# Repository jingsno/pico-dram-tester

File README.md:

# Pico DRAM Tester

Having trouble with your old-school DIP dynamic RAM chips? Here's a simple
RAM tester that will give you a definitive pass or fail for a variety of
chips.

**New** rev 3 now available! New features include:

* USB-C power connector with PD resistors
* Universal encoder wiring supports Bourns and Panasonic style encoders
* Through-hole footprint for the Pico2 to ease soldering

Benefits

* Tests RAM *at full speed* so you can feel confident about a chip that passes.
* Easy to construct with widely-available parts. No surface mount chips.
* Low cost
* Built-in DC-DC modules generate extra voltages required by 4116-class chips
* Can be operated from a bench supply for voltage margin testing

Supported Devices

* 4027 (4K x 1)
* 4108 (8K x 1 that are 4116s with only half test good: MK4108, TMS4108, etc)
* 4116 (16K x 1)
* 4132 (32K x 1, piggyback)
* 4132 (32K x 1 that are 4164s with only half tested good: TMS4532, M3732)
* 4164 (64K x 1)
* 41128 (128K x 1, piggyback)
* 41256 (256K x 1)
* 4416 (16K x 4)
* 4464 (64K x 4)
* 44256 (256K x 4)

Out of scope

* SRAM, DRAM chips larger than 1MBit
* Logic chips

## Construction

[Fab package](fab/pico-dram-tester-rev3.zip)

[Schematic](pico-dram-tester.pdf)

[Bill of Materials](pico-dram-tester.csv)

The board is a simple 2-layer board, 100mm x 100mm, and 1.6mm thick. Fabricate
at your favorite vendor in any color you wish.

You may populate the board only with the sockets for devices you plan to use,
or you may populate all the sockets. You can try substituting the sockets with
standard IC sockets, but I recommend ZIF sockets which are much easier to use.
Why so many sockets? It saves you from having to install dozens of pin control
transistors required to make a tester work with a single universal socket.

If you want to populate the USB-C connector, do it first before any other
components. It makes it much easier to access the surface-mount pins along
the edge with a soldering iron.

Populate Q1, U7, U8, R2, R3, R4, and R5 if you would like to test 4116 and
4132 devices without requiring an external -5V and +12V power supply.

If you want to provide the -5V, +5V, and +12V power from your bench supply,
then you may leave those components off of the board and connect your power
leads to the -5V, +5V, and +12V test points. If you don't plan to test 4116
or 4132 chips, then you can safely leave out those components.

The LCD display is nominally the [Adafruit 4383](https://www.adafruit.com/product/4383) which is to be installed at location J1 (U9 is not required when using
this display). You can also use cheaper devices available from Aliexpress and
others. They are 8-pin LCD displays sold as 1.14" 135x240 IPS ST7789 modules.
Install this display at position J2. You may also need to add the voltage
monitor at position U9.

For several reasons, this board requires a Pico 2 microcontroller board and
will not work at all with the Pico 1.

If you use a Bourns-style encoder, you will need to solder across the jumper
on the back of the board. **This is the most common type of cheaply-available
encoders, so you probably want to do this.** Otherwise, for Panasonic-style
encoders, leave this open.

After installing all the components and inspecting the board for accidental
short circuits, connect the Pico 2 via the USB connector to a computer. The
device should power up and appear as a USB mass storage device. Copy the
prebuilt firmware file [pmemtest.uf2](firmware/pmemtest.uf2) to this device, and the Pico 2 will
program itself. Reset the power and you should see a menu of chips on the LCD
screen.

## Using the DRAM Tester

Before starting, connect the tester to a power source:

* If you did not install U7 and U8, connect a bench supply to the GND, -5V, +5V, and +12V test points. Connect the Pico 2 USB jack to a power adapter or computer.
* If you installed U7 and U8, connect a 5V bench supply to the 5VIN and GND test points. Instead of a bench supply, you could connect the Pico 2 USB jack to a power adapter, but you won't be able to control the voltage. A computer often has a much lower voltage and you may fail RAM chips that actually function at 5V.

1. Install the chip in the socket designated for that type of memory chip, following the pin 1 orientation (the pin 1 notch faces the ZIF socket lever). Note that some of the sockets are used for several types of memory.
2. Rotate the selection knob until the correct part number is highlighted, and push down on the top of the selection knob (it's also a button!)
3. If you make a mistake, press the button to the left of the selection knob to go back.
4. After selecting a part, you need to pick the correct speed grade to run the
test. Often the speed grade is marked on the chip as a suffix. For example, -15
typically means 150ns. If you're not sure, pick the slowest speed.
5. If you are using an external bench power supply to supply -5V and +12V, turn it on now. If you soldered in the on-board voltage converter modules, you don't need to do anything. Push the top of the selection knob to continue.
6. The test runs. You will see a red "X" if the test fails or a green checkmark if the test passes.
7. You can rerun the test immediately by pushing down on the top of the selection knob. Or go back to the menu by pushing the button to the left.

Note: The visualization pane on the left is just for entertainment and doesn't
really represent bad bits.

## Technical Details

The Pico 2 microcontroller (RP2350) has built-in high-speed PIO processors
which are overclocked to 300MHz. This means that the DRAM timing can be set
to a resolution of 3.3ns. The RAM test runs on the second CPU core, decoupling
it from the GUI, which runs on the first CPU core.

RAM testing can be surprisingly complicated. There are many kinds of failures:

* Stuck-at fault - a cell is stuck at a 1 or a 0
* Stuck-open fault - a cell isn't connected (input or output)
* Transition fault - a cell can't go from one state to another (1 to 0 or 0 to 1)
* Data retention fault - a cell flips after a time delay
* Coupling fault - the state of one cell affects the state of another
* Neighborhood pattern sensitive fault - a specific pattern in nearby cells causes a cell to flip
* Address decoder fault - cells may be isolated, or multiple cells accessed at the same address, or multiple addresses may access a single cell

There are a number of "traditional" RAM tests such as the checkerboard or
walking 1/0, but these tests can be slow and don't have precise coverage over
all failure modes. The Pico DRAM Tester uses more modern testing algorithms:

* March-B. This is a sequence of linear reads and writes designed to catch address faults, stuck-at faults, transition faults, and coupling faults.
* Pseudorandom test. This test loads a pseudorandom number sequence into the memory, reads it back, and checks to make sure it didn't change. The test is repeated with 64 different pseudorandom patterns to enhance coverage. The patterns are identical between runs, making the test repeatable. The test only uses pseudorandom data and does not randomize the address. This test can detect many pattern-sensitive faults.
* Refresh test. This test loads a pattern into the memory, waits for a time delay, and then tries to read it back. The time delay is longer than a typical refresh rate. This test can detect data retention faults.

## Known Issues

* The 41128 test is not yet reliable.

## Troubleshooting

Check your solder connections. Does the Pico 2 board show up in bootloader mode when you plug it into a computer?

The Pico DRAM Tester uses an overclocked Pico 2 configuration.
Some Pico 2 boards may not work well at 300MHz, crashing or not drawing the GUI on the screen correctly.
You may be able to get it working by editing pmemtest.c, find the line `vreg_set_voltage(VREG_VOLTAGE_1_15);` and change the voltage setting to `VREG_VOLTAGE_1_20`.

## License

This work is licensed under a Creative Commons Attribution-ShareAlike 4.0
International License. See [https://creativecommons.org/licenses/by-sa/4.0/](https://creativecommons.org/licenses/by-sa/4.0/).

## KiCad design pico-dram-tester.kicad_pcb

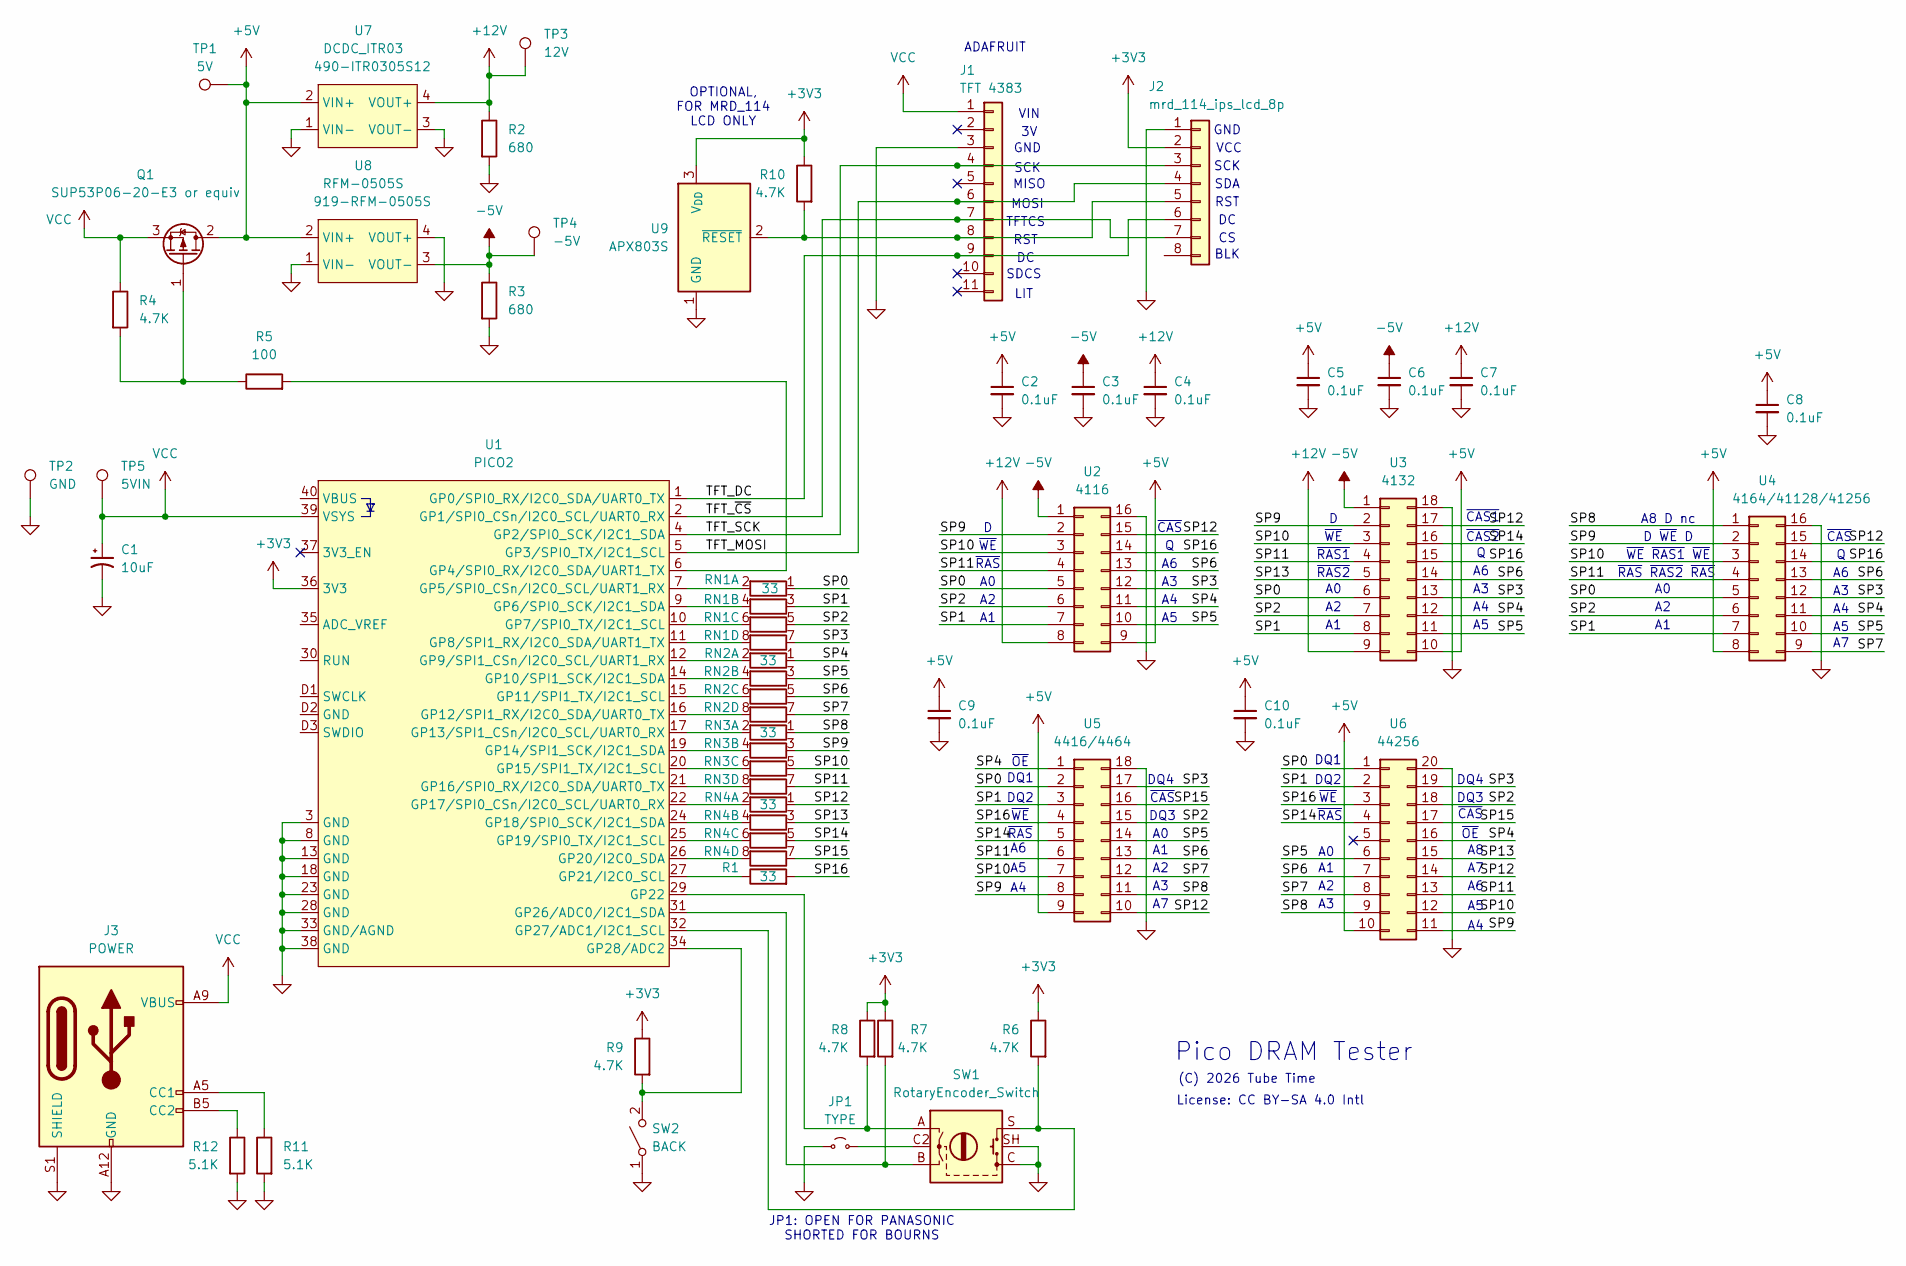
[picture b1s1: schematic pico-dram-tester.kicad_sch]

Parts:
C1: 10uF; CAPAE200P500X1100; Mouser 667-ECA-1VM100
C2, C3, C4, C5, C6, C7, C8, C9, C10: 0.1uF; CAPAC200; Mouser 80-C322C104M5U
J1: TFT 4383; ADAFRUIT_4383
J2: mrd_114_ips_lcd_8p; PinHeader_1x08_P2.54mm_Vertical
J3: POWER; USB_C_Receptacle_GCT_USB4125-xx-x-0190_6P_TopMnt_Horizontal; Mouser 179-UJCHGSMT1P6TR
JP1: TYPE; SolderJumper-2_P1.3mm_Open_Pad1.0x1.5mm
Q1: SUP53P06-20-E3 or equiv; TO-220-3_Vertical; Mouser 781-SUP53P06-20-E3
R1: 33; RESA500; Mouser 594-MBB02070C3309FCT
R2, R3: 680; RESA500; Mouser 594-MBB02070C6800FCT
R4, R6, R7, R8, R9, R10: 4.7K; RESA500; Mouser 594-MBB02070C4701FCT
R5: 100; RESA500; Mouser 594-MBB02070C1000FCT
R11, R12: 5.1K; RESA500; Mouser 594-MBB02070C5101FCT
RN1, RN2, RN3, RN4: 33; R_Array_SIP8; Mouser 652-4608X-2LF-33
SW1: RotaryEncoder_Switch; ENCODER_SW_UNIV
SW2: BACK; SW_SPST_Omron_B3F-50xx; Mouser 653-B3F-4005
TP1: 5V; TestPoint_Keystone_5005-5009_Compact; Mouser 534-5005
TP2: GND; TestPoint_Keystone_5005-5009_Compact; Mouser 534-5006
TP3: 12V; TestPoint_Keystone_5005-5009_Compact; Mouser 534-5009
TP4: -5V; TestPoint_Keystone_5005-5009_Compact; Mouser 534-5007
TP5: 5VIN; TestPoint_Keystone_5005-5009_Compact; Mouser 534-5005
U1: PICO2; Pico2_PTH; Mouser 358-SC1631
U2: 4116; DIP_Socket-16_W4.3_W5.08_W7.62_W10.16_W10.9_3M_216-3340-00-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
U3: 4132; DIP_Socket-18_W4.3_W5.08_W7.62_W10.16_W10.9_3M_218-3341-00-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
U4: 4164/41128/41256; DIP_Socket-16_W4.3_W5.08_W7.62_W10.16_W10.9_3M_216-3340-00-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
U5: 4416/4464; DIP_Socket-18_W4.3_W5.08_W7.62_W10.16_W10.9_3M_218-3341-00-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
U6: 44256; DIP_Socket-20_W4.3_W5.08_W7.62_W10.16_W10.9_3M_220-3342-00-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
U7: DCDC_ITR03; Mouser 490-ITR0305S12
U8: RFM-0505S; DCDC_ITR03; Mouser 919-RFM-0505S
U9: APX803S; SOT-23_Handsoldering; Mouser 621-APX803S-29SA-7

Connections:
+3V3: J2.2, R6.1, R7.1, R8.1, R9.1, R10.1, U1.36 (3V3), U9.3 (V_{DD})
+5V: C2.1, C5.1, C8.1, C9.1, C10.1, Q1.2 (D), TP1.1, U2.9, U3.10, U4.8, U5.9, U6.10, U7.2 (VIN+), U8.2 (VIN+)
+12V: C4.1, C7.1, R2.1, TP3.1, U2.8, U3.9, U7.4 (VOUT+)
-5V: C3.1, C6.1, R3.1, TP4.1, U2.1, U3.1, U8.3 (VOUT-)
/SP0: RN1.1 (R1.1), U2.5, U3.6, U4.5, U5.2, U6.1
/SP1: RN1.3 (R2.1), U2.7, U3.8, U4.7, U5.3, U6.2
/SP2: RN1.5 (R3.1), U2.6, U3.7, U4.6, U5.15, U6.18
/SP3: RN1.7 (R4.1), U2.12, U3.13, U4.12, U5.17, U6.19
/SP4: RN2.1 (R1.1), U2.11, U3.12, U4.11, U5.1, U6.16
/SP5: RN2.3 (R2.1), U2.10, U3.11, U4.10, U5.14, U6.6
/SP6: RN2.5 (R3.1), U2.13, U3.14, U4.13, U5.13, U6.7
/SP7: RN2.7 (R4.1), U4.9, U5.12, U6.8
/SP8: RN3.1 (R1.1), U4.1, U5.11, U6.9
/SP9: RN3.3 (R2.1), U2.2, U3.2, U4.2, U5.8, U6.11
/SP10: RN3.5 (R3.1), U2.3, U3.3, U4.3, U5.7, U6.12
/SP11: RN3.7 (R4.1), U2.4, U3.4, U4.4, U5.6, U6.13
/SP12: RN4.1 (R1.1), U2.15, U3.17, U4.15, U5.10, U6.14
/SP13: RN4.3 (R2.1), U3.5, U6.15
/SP14: RN4.5 (R3.1), U3.16, U5.5, U6.4
/SP15: RN4.7 (R4.1), U5.16, U6.17
/SP16: R1.2, U2.14, U3.15, U4.14, U5.4, U6.3
/TFT_DC: J1.9, J2.6, U1.1 (GP0/SPI0_RX/I2C0_SDA/UART0_TX)
/TFT_MOSI: J1.6, J2.4, U1.5 (GP3/SPI0_TX/I2C1_SCL)
/TFT_SCK: J1.4, J2.3, U1.4 (GP2/SPI0_SCK/I2C1_SDA)
/TFT_~CS: J1.7, J2.7, U1.2 (GP1/SPI0_CSn/I2C0_SCL/UART0_RX)
GND: C1.2, C2.2, C3.2, C4.2, C5.2, C6.2, C7.2, C8.2, C9.2, C10.2, J1.3, J2.1, J3.A12 (GND), J3.B12 (GND), J3.S1 (SHIELD), JP1.1 (A), R2.2, R3.2, R11.2, R12.2, SW1.C, SW1.SH, SW2.1 (A), TP2.1, U1.3 (GND), U1.8 (GND), U1.13 (GND), U1.18 (GND), U1.23 (GND), U1.28 (GND), U1.33 (GND/AGND), U1.38 (GND), U2.16, U3.18, U4.16, U5.18, U6.20, U7.1 (VIN-), U7.3 (VOUT-), U8.1 (VIN-), U8.4 (VOUT+), U9.1 (GND)
unnamed: J1.8, J2.5, R10.2, U9.2 (~RESET)
unnamed: J3.A5 (CC1), R11.1
unnamed: J3.B5 (CC2), R12.1
unnamed: JP1.2 (B), SW1.C2 (C)
unnamed: Q1.1 (G), R4.2, R5.1
unnamed: RN1.2 (R1.2), U1.7 (GP5/SPI0_CSn/I2C0_SCL/UART1_RX)
unnamed: RN1.4 (R2.2), U1.9 (GP6/SPI0_SCK/I2C1_SDA)
unnamed: RN1.6 (R3.2), U1.10 (GP7/SPI0_TX/I2C1_SCL)
unnamed: RN1.8 (R4.2), U1.11 (GP8/SPI1_RX/I2C0_SDA/UART1_TX)
unnamed: RN2.2 (R1.2), U1.12 (GP9/SPI1_CSn/I2C0_SCL/UART1_RX)
unnamed: RN2.4 (R2.2), U1.14 (GP10/SPI1_SCK/I2C1_SDA)
unnamed: RN2.6 (R3.2), U1.15 (GP11/SPI1_TX/I2C1_SCL)
unnamed: RN2.8 (R4.2), U1.16 (GP12/SPI1_RX/I2C0_SDA/UART0_TX)
unnamed: RN3.2 (R1.2), U1.17 (GP13/SPI1_CSn/I2C0_SCL/UART0_RX)
unnamed: RN3.4 (R2.2), U1.19 (GP14/SPI1_SCK/I2C1_SDA)
unnamed: RN3.6 (R3.2), U1.20 (GP15/SPI1_TX/I2C1_SCL)
unnamed: RN3.8 (R4.2), U1.21 (GP16/SPI0_RX/I2C0_SDA/UART0_TX)
unnamed: RN4.2 (R1.2), U1.22 (GP17/SPI0_CSn/I2C0_SCL/UART0_RX)
unnamed: RN4.4 (R2.2), U1.24 (GP18/SPI0_SCK/I2C1_SDA)
unnamed: RN4.6 (R3.2), U1.25 (GP19/SPI0_TX/I2C1_SCL)
unnamed: RN4.8 (R4.2), U1.26 (GP20/I2C0_SDA)
unnamed: R9.2, SW2.2 (B), U1.34 (GP28/ADC2)
unnamed: R5.2, U1.6 (GP4/SPI0_RX/I2C0_SDA/UART1_TX)
unnamed: R1.1, U1.27 (GP21/I2C0_SCL)
unnamed: R8.2, SW1.A, U1.29 (GP22)
unnamed: R7.2, SW1.B, U1.31 (GP26/ADC0/I2C1_SDA)
unnamed: R6.2, SW1.S, U1.32 (GP27/ADC1/I2C1_SCL)
VCC: C1.1, J1.1, J3.A9 (VBUS), J3.B9 (VBUS), Q1.3 (S), R4.1, TP5.1, U1.39 (VSYS)

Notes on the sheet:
~{OE}
~{CAS}
~{RAS}
ADAFRUIT
GND
BLK
LIT
~{WE}
~{CAS2}
~{CAS1}
License: CC BY-SA 4.0 Intl
MOSI
DQ2
SDCS
(C) 2026 Tube Time
DQ3
~{RAS} ~{RAS2} ~{RAS}
OPTIONAL, FOR MRD_114 LCD ONLY
A8 D nc
DQ1
TFTCS
JP1: OPEN FOR PANASONIC SHORTED FOR BOURNS
DQ4
SCK
~{RAS1}
~{RAS2}
VIN
SDA
VCC
Pico DRAM Tester
D ~{WE} D
~{WE} ~{RAS1} ~{WE}
RST
MISO

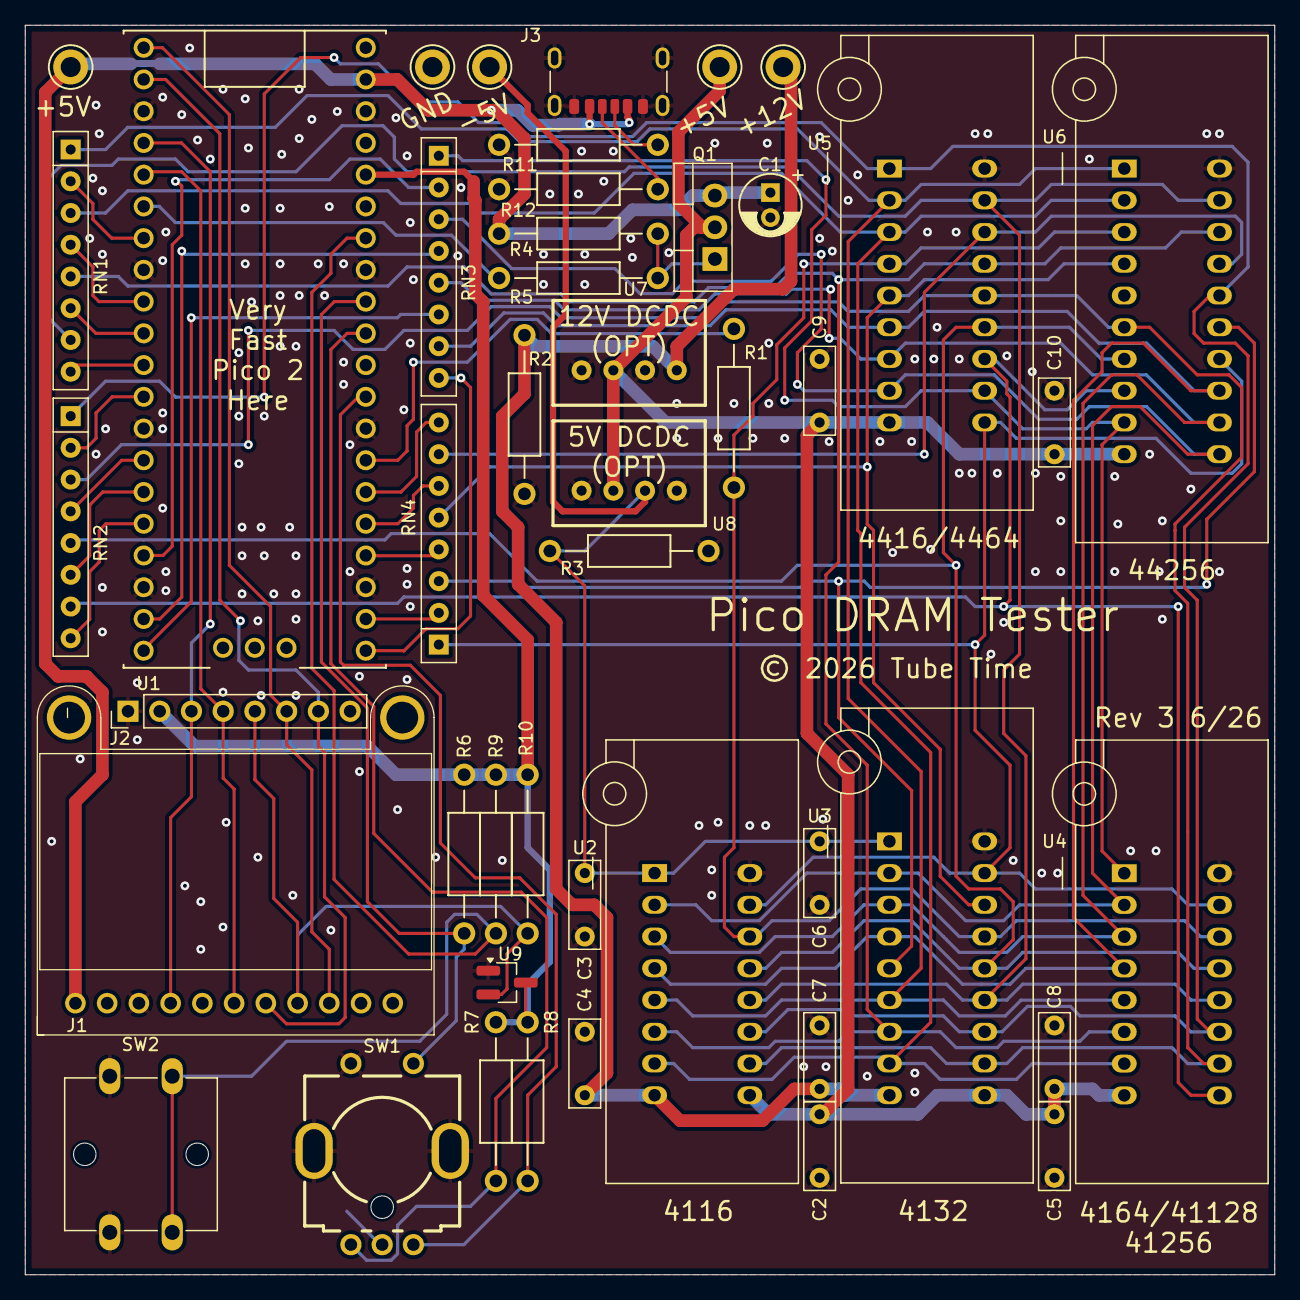
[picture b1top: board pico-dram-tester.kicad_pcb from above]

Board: 2 copper layers, 100.0 x 100.0 mm, 47 parts (1 on the bottom side), 54 nets.

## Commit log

2025-09-22 Added 4164 120ns/150ns variants with longer tWCH delay
    Added 4164 120ns/150ns variants with longer tWCH delay
    Some 4164 brands needs longer tWCH delay than the default settings
2025-09-22 Uploaded compiled firmware

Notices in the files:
pico-dram-tester.kicad_pcb:
© 2026 Tube Time
